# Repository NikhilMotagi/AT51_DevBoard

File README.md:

# AT51

Arduino Nano-style development board for the AT89S51 (8051-compatible) microcontroller.

AT51 is an open-source development board designed to bring the classic 8051 architecture into a modern, breadboard-friendly form factor. The project was created to showcase PCB design skills while providing a compact development platform for learning and experimenting with 8051-based microcontrollers.

---

## Features

- Arduino Nano-inspired footprint
- Based on the AT89S51 microcontroller
- USB connectivity through FT232RL
- On-board programming interface
- Port-wise GPIO breakout
- Power status LED
- UART TX/RX activity LEDs
- Compact and breadboard-friendly layout

---

## Hardware Specifications

| Parameter | Value |
|------------|---------|
| MCU | AT89S51 |
| Architecture | 8051 Compatible |
| Operating Voltage | 5V |
| Clock Frequency | 11.0592 MHz |
| USB Interface | FT232RL |
| Form Factor | Arduino Nano Style |

---

## Design Goals

The objective of this project was to:

- Create a compact 8051 development platform
- Modernize the development experience for legacy microcontrollers
- Demonstrate PCB design and hardware integration skills
- Provide an open-source reference design for students and hobbyists

---

## Repository Contents

```text
/
├── Project File/
│   ├── Schematic Files
│   ├── PCB Layout
│
├── Gerbers/
│   └── Manufacturing Files
│
├── Images/
│
└── README.md
```

---

## Images

### PCB Render

  |||
  |--|--|
  |||

### Layout

|||
|--|--|

---

## Manufacturing Status

> ⚠️ Design Complete — Not Yet Manufactured

This repository currently contains the completed design files and manufacturing outputs. Physical prototypes have not yet been fabricated or tested.

---

## License

This project is released under the MIT License.

See the `LICENSE` file for details.

---

## Author

Designed by **Nikhil Motagi**.

If you find this project useful, feel free to star the repository and share your feedback.

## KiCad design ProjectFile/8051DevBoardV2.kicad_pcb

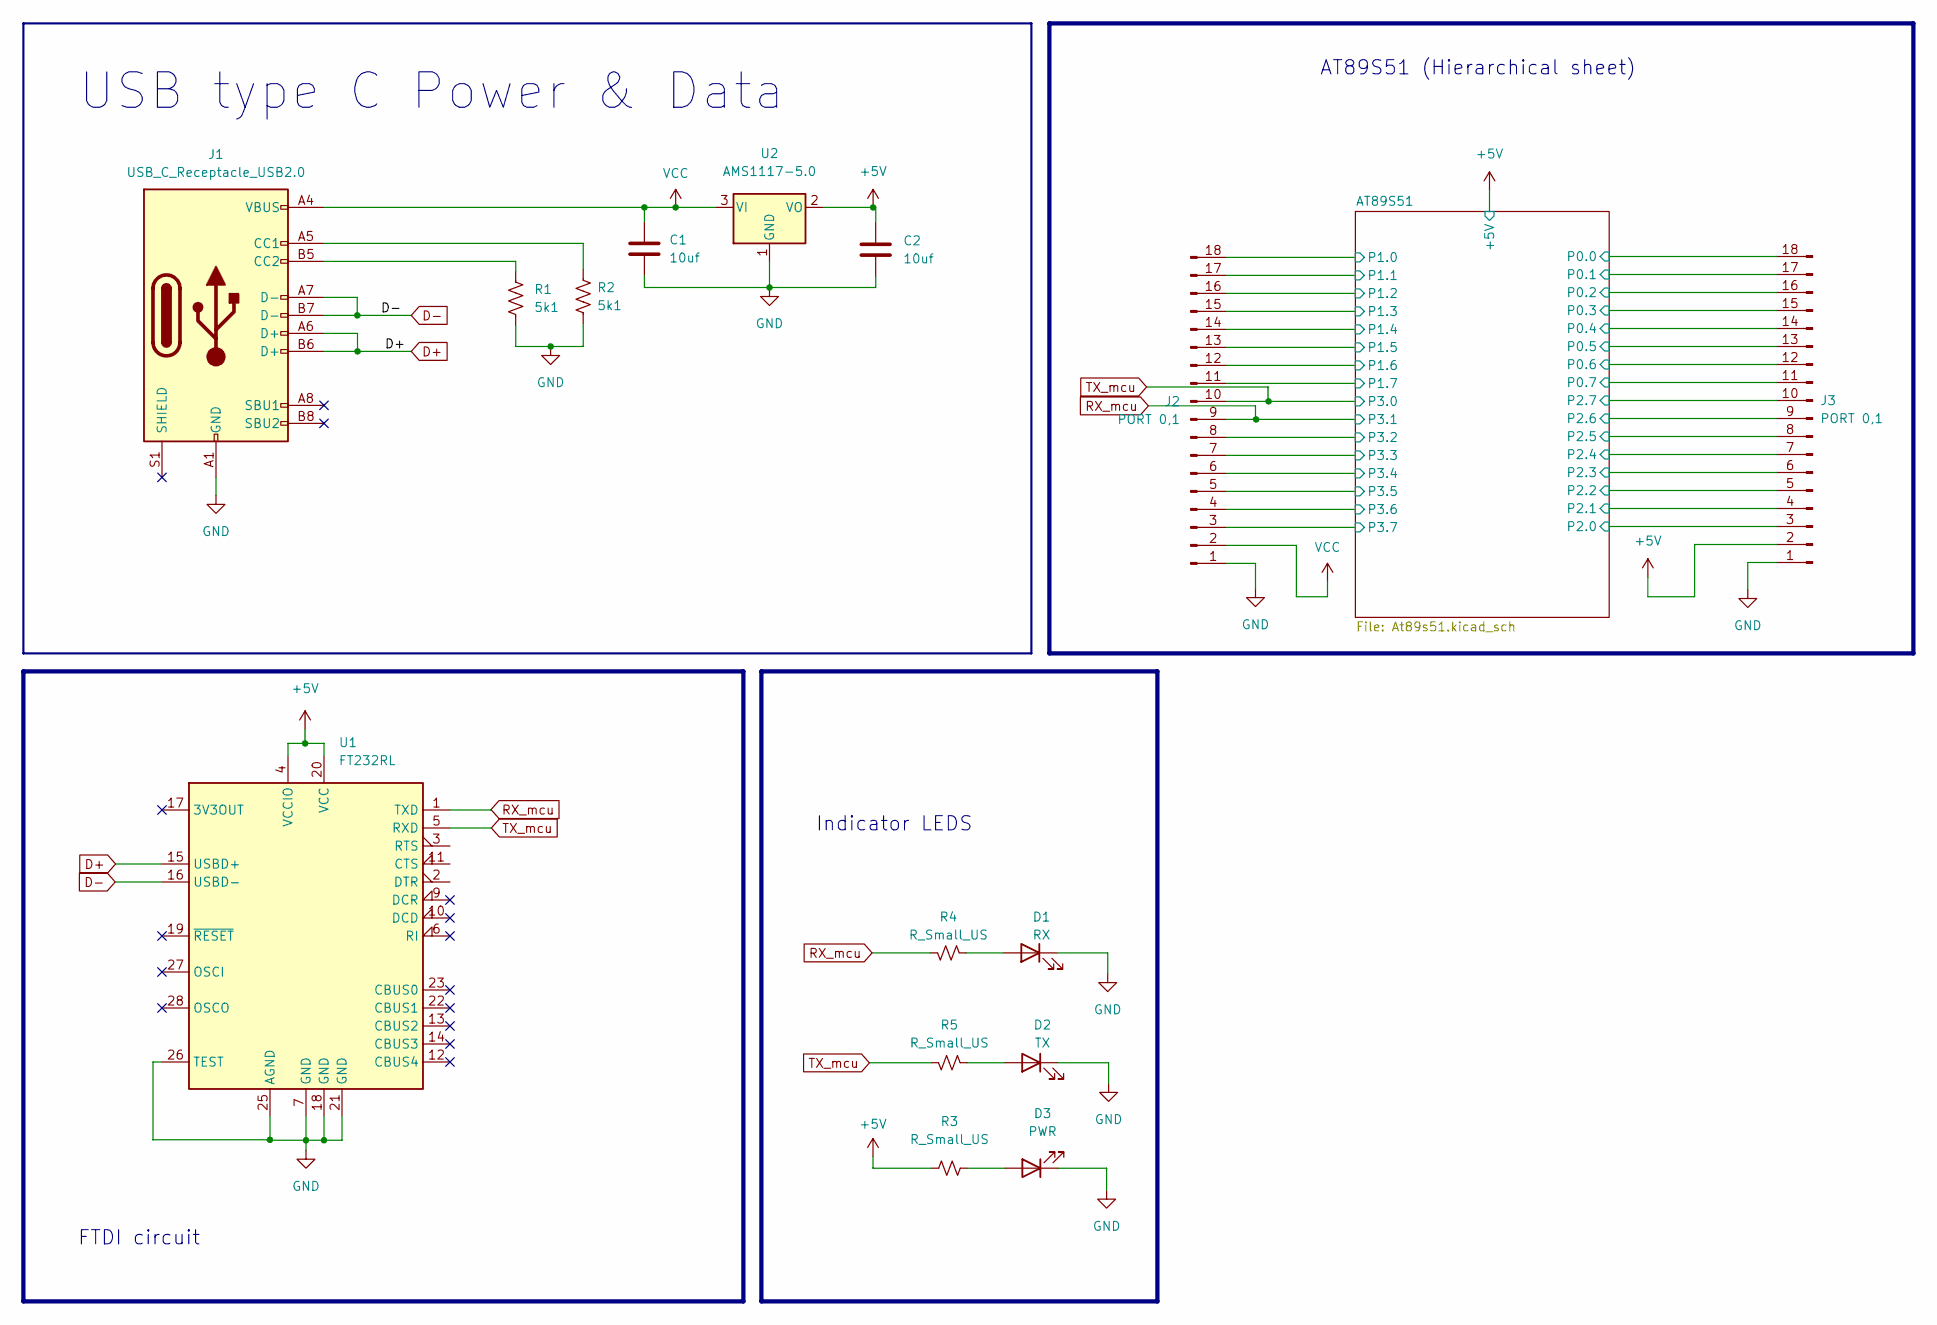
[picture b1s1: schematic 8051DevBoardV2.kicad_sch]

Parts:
C1, C2: 10uf; C_0402_1005Metric
D1: RX; LED_0402_1005Metric
D2: TX; LED_0402_1005Metric
D3: PWR; LED_0402_1005Metric
J1: USB_C_Receptacle_USB2.0; USB_C_Receptacle_HRO_TYPE-C-31-M-12
J2, J3: PORT 0,1; PinHeader_1x18_P2.54mm_Vertical
R1, R2: 5k1; R_0402_1005Metric
R3, R4, R5: R_Small_US; R_0402_1005Metric
U1: FT232RL; SSOP-28_5.3x10.2mm_P0.65mm
U2: AMS1117-5.0; SOT-223-3_TabPin2

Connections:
+5V: C2.1, J3.2, R3.1, U1.4 (VCCIO), U1.20 (VCC), U2.2 (VO); also elsewhere on the board
/AT89S51/P0.0: J3.18; also elsewhere on the board
/AT89S51/P0.1: J3.17; also elsewhere on the board
/AT89S51/P0.2: J3.16; also elsewhere on the board
/AT89S51/P0.3: J3.15; also elsewhere on the board
/AT89S51/P0.4: J3.14; also elsewhere on the board
/AT89S51/P0.5: J3.13; also elsewhere on the board
/AT89S51/P0.6: J3.12; also elsewhere on the board
/AT89S51/P0.7: J3.11; also elsewhere on the board
/AT89S51/P1.0: J2.18; also elsewhere on the board
/AT89S51/P1.1: J2.17; also elsewhere on the board
/AT89S51/P1.2: J2.16; also elsewhere on the board
/AT89S51/P1.3: J2.15; also elsewhere on the board
/AT89S51/P1.4: J2.14; also elsewhere on the board
/AT89S51/P1.5: J2.13; also elsewhere on the board
/AT89S51/P1.6: J2.12; also elsewhere on the board
/AT89S51/P1.7: J2.11; also elsewhere on the board
/AT89S51/P2.0: J3.3; also elsewhere on the board
/AT89S51/P2.1: J3.4; also elsewhere on the board
/AT89S51/P2.2: J3.5; also elsewhere on the board
/AT89S51/P2.3: J3.6; also elsewhere on the board
/AT89S51/P2.4: J3.7; also elsewhere on the board
/AT89S51/P2.5: J3.8; also elsewhere on the board
/AT89S51/P2.6: J3.9; also elsewhere on the board
/AT89S51/P2.7: J3.10; also elsewhere on the board
/AT89S51/P3.2: J2.8; also elsewhere on the board
/AT89S51/P3.3: J2.7; also elsewhere on the board
/AT89S51/P3.4: J2.6; also elsewhere on the board
/AT89S51/P3.5: J2.5; also elsewhere on the board
/AT89S51/P3.6: J2.4; also elsewhere on the board
/AT89S51/P3.7: J2.3; also elsewhere on the board
D+: J1.A6 (D+), J1.B6 (D+), U1.15 (USBD+)
D-: J1.A7 (D-), J1.B7 (D-), U1.16 (USBD-)
GND: C1.2, C2.2, D1.1 (K), D2.1 (K), D3.1 (K), J1.A1 (GND), J1.A12 (GND), J1.B1 (GND), J1.B12 (GND), J2.1, J3.1, R1.2, R2.2, U1.7 (GND), U1.18 (GND), U1.21 (GND), U1.25 (AGND), U1.26 (TEST), U2.1 (GND); also elsewhere on the board
unnamed: D1.2 (A), R4.2
unnamed: D2.2 (A), R5.2
unnamed: D3.2 (A), R3.2
unnamed: J1.A5 (CC1), R2.1
unnamed: J1.B5 (CC2), R1.1
RX_mcu: J2.9, R4.1, U1.1 (TXD); also elsewhere on the board
TX_mcu: J2.10, R5.1, U1.5 (RXD); also elsewhere on the board
VCC: C1.1, J1.A4 (VBUS), J1.A9 (VBUS), J1.B4 (VBUS), J1.B9 (VBUS), J2.2, U2.3 (VI)

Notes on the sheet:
AT89S51 (Hierarchical sheet)
FTDI circuit
USB type C Power & Data
Indicator LEDS

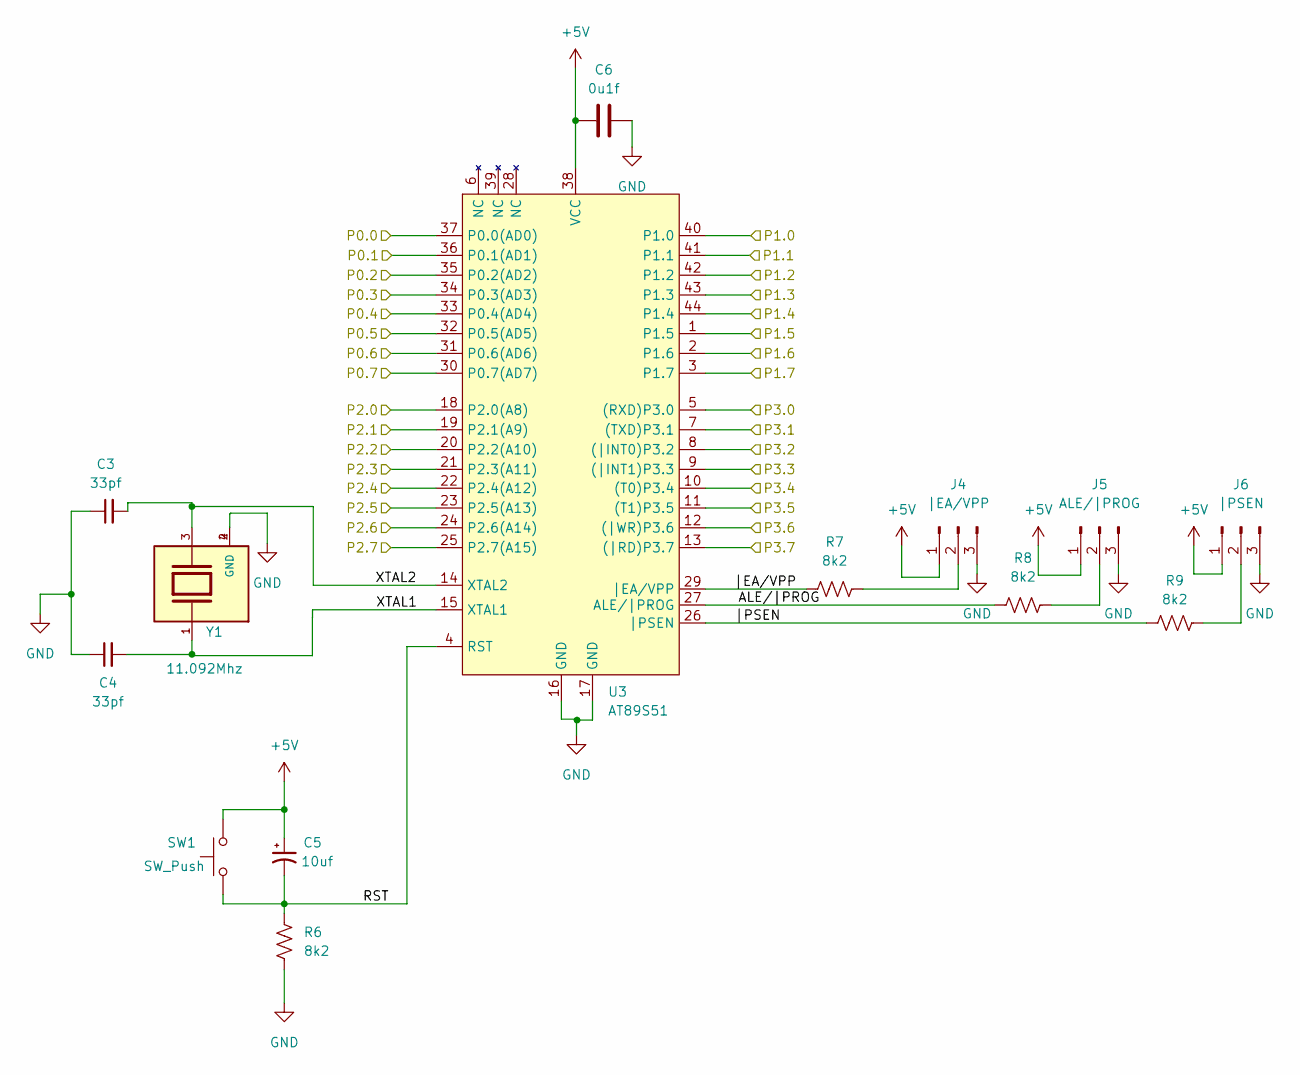
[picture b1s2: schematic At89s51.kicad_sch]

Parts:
C3, C4: 33pf; C_0402_1005Metric
C5: 10uf; C_0402_1005Metric
C6: 0u1f; C_0402_1005Metric
J4: |EA/VPP; PinHeader_1x03_P2.54mm_Vertical
J5: ALE/|PROG; PinHeader_1x03_P2.54mm_Vertical
J6: |PSEN; PinHeader_1x03_P2.54mm_Vertical
R6, R7, R8, R9: 8k2; R_0402_1005Metric
SW1: SW_Push; SW_SPST_B3U-1000P
U3: AT89S51; TQFP-44_10x10mm_P0.8mm
Y1: 11.092Mhz; XTAL_ABM3B-11.0592MHZ-10-1-U-T; PARTREV 08.25.15

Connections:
+5V: C5.1, C6.1, J4.1, J5.1, J6.1, SW1.2, U3.38 (VCC); also elsewhere on the board
/AT89S51/ALE/|PROG: R8.1, U3.27 (ALE/|PROG)
/AT89S51/P0.0: U3.37 (P0.0(AD0)); also elsewhere on the board
/AT89S51/P0.1: U3.36 (P0.1(AD1)); also elsewhere on the board
/AT89S51/P0.2: U3.35 (P0.2(AD2)); also elsewhere on the board
/AT89S51/P0.3: U3.34 (P0.3(AD3)); also elsewhere on the board
/AT89S51/P0.4: U3.33 (P0.4(AD4)); also elsewhere on the board
/AT89S51/P0.5: U3.32 (P0.5(AD5)); also elsewhere on the board
/AT89S51/P0.6: U3.31 (P0.6(AD6)); also elsewhere on the board
/AT89S51/P0.7: U3.30 (P0.7(AD7)); also elsewhere on the board
/AT89S51/P1.0: U3.40 (P1.0); also elsewhere on the board
/AT89S51/P1.1: U3.41 (P1.1); also elsewhere on the board
/AT89S51/P1.2: U3.42 (P1.2); also elsewhere on the board
/AT89S51/P1.3: U3.43 (P1.3); also elsewhere on the board
/AT89S51/P1.4: U3.44 (P1.4); also elsewhere on the board
/AT89S51/P1.5: U3.1 (P1.5); also elsewhere on the board
/AT89S51/P1.6: U3.2 (P1.6); also elsewhere on the board
/AT89S51/P1.7: U3.3 (P1.7); also elsewhere on the board
/AT89S51/P2.0: U3.18 (P2.0(A8)); also elsewhere on the board
/AT89S51/P2.1: U3.19 (P2.1(A9)); also elsewhere on the board
/AT89S51/P2.2: U3.20 (P2.2(A10)); also elsewhere on the board
/AT89S51/P2.3: U3.21 (P2.3(A11)); also elsewhere on the board
/AT89S51/P2.4: U3.22 (P2.4(A12)); also elsewhere on the board
/AT89S51/P2.5: U3.23 (P2.5(A13)); also elsewhere on the board
/AT89S51/P2.6: U3.24 (P2.6(A14)); also elsewhere on the board
/AT89S51/P2.7: U3.25 (P2.7(A15)); also elsewhere on the board
/AT89S51/P3.2: U3.8 ((|INT0)P3.2); also elsewhere on the board
/AT89S51/P3.3: U3.9 ((|INT1)P3.3); also elsewhere on the board
/AT89S51/P3.4: U3.10 ((T0)P3.4); also elsewhere on the board
/AT89S51/P3.5: U3.11 ((T1)P3.5); also elsewhere on the board
/AT89S51/P3.6: U3.12 ((|WR)P3.6); also elsewhere on the board
/AT89S51/P3.7: U3.13 ((|RD)P3.7); also elsewhere on the board
/AT89S51/RST: C5.2, R6.1, SW1.1, U3.4 (RST)
/AT89S51/XTAL1: C4.2, U3.15 (XTAL1), Y1.1
/AT89S51/XTAL2: C3.2, U3.14 (XTAL2), Y1.3
/AT89S51/|EA/VPP: R7.1, U3.29 (|EA/VPP)
/AT89S51/|PSEN: R9.1, U3.26 (|PSEN)
GND: C3.1, C4.1, C6.2, J4.3, J5.3, J6.3, R6.2, U3.16 (GND), U3.17 (GND), Y1.2 (GND), Y1.4 (GND); also elsewhere on the board
unnamed: J4.2, R7.2
unnamed: J5.2, R8.2
unnamed: J6.2, R9.2
RX_mcu: U3.7 ((TXD)P3.1); also elsewhere on the board
TX_mcu: U3.5 ((RXD)P3.0); also elsewhere on the board

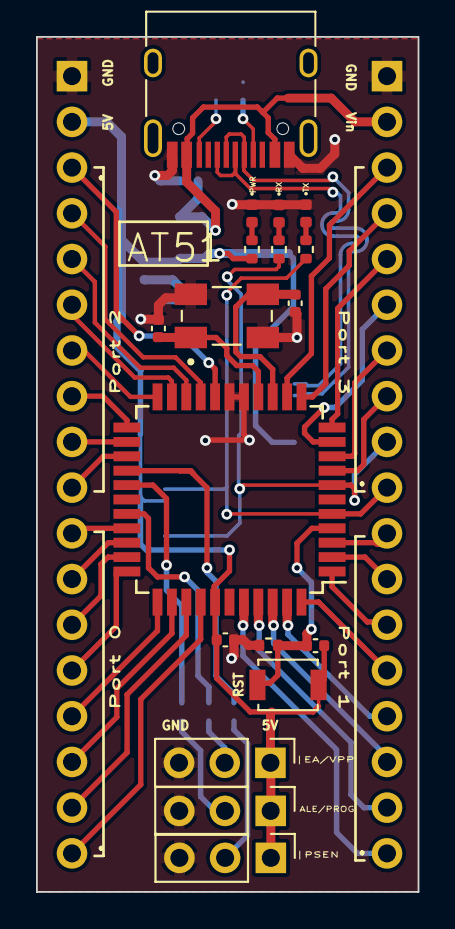
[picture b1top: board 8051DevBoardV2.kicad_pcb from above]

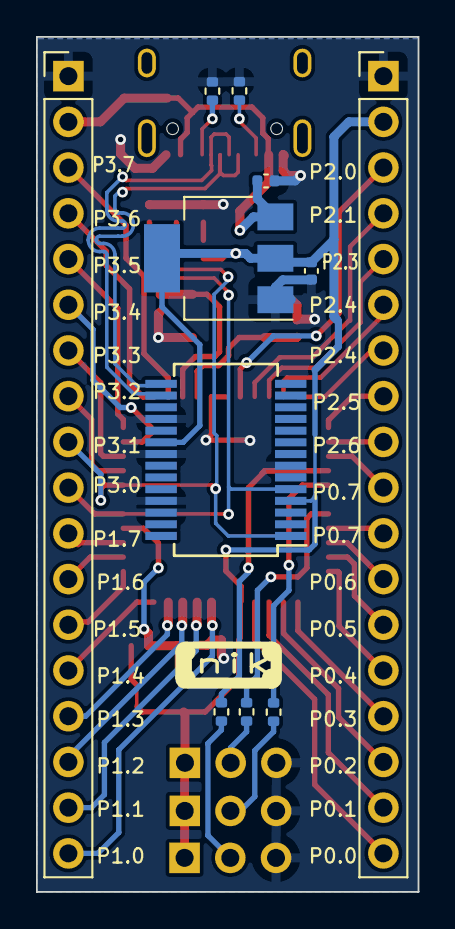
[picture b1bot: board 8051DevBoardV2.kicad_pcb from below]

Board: 2 copper layers, 21.2 x 47.5 mm, 29 parts (11 on the bottom side), 51 nets.

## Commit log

2026-05-31 Push main project
2026-05-31 Push project images

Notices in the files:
README.md:
License: MIT
